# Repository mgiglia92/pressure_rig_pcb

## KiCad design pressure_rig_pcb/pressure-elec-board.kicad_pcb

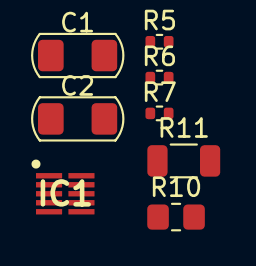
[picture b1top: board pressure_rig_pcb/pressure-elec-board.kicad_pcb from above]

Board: 2 copper layers, 8 parts (0 on the bottom side), 7 nets, no tracks yet.

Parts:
C1, C2: .1 uF; C_1206_3216Metric_Pad1.42x1.75mm
IC1: DAC82001DRXR; SON50P250X250X80-10N
R5, R6: 10 k; R_0402_1005Metric
R7: 5 k; R_0402_1005Metric
R10: 158k; R_0805_2012Metric_Pad1.20x1.40mm_HandSolder
R11: 30.1k; R_1206_3216Metric

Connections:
3.3V: C2.2 (-), IC1.10 (VREF)
5V: C1.2 (-), IC1.1 (VDD), R7.1 (+)
DAC_ACTIVE: IC1.7 (~SYNC), R7.2 (-)
GND: IC1.4 (AGND), R5.1 (+), R6.1 (+), R11.2
unnamed: IC1.3 (RSTSEL), R5.2 (-)
unnamed: IC1.5 (~RESET), R6.2 (-)
unnamed: R10.1, R11.1

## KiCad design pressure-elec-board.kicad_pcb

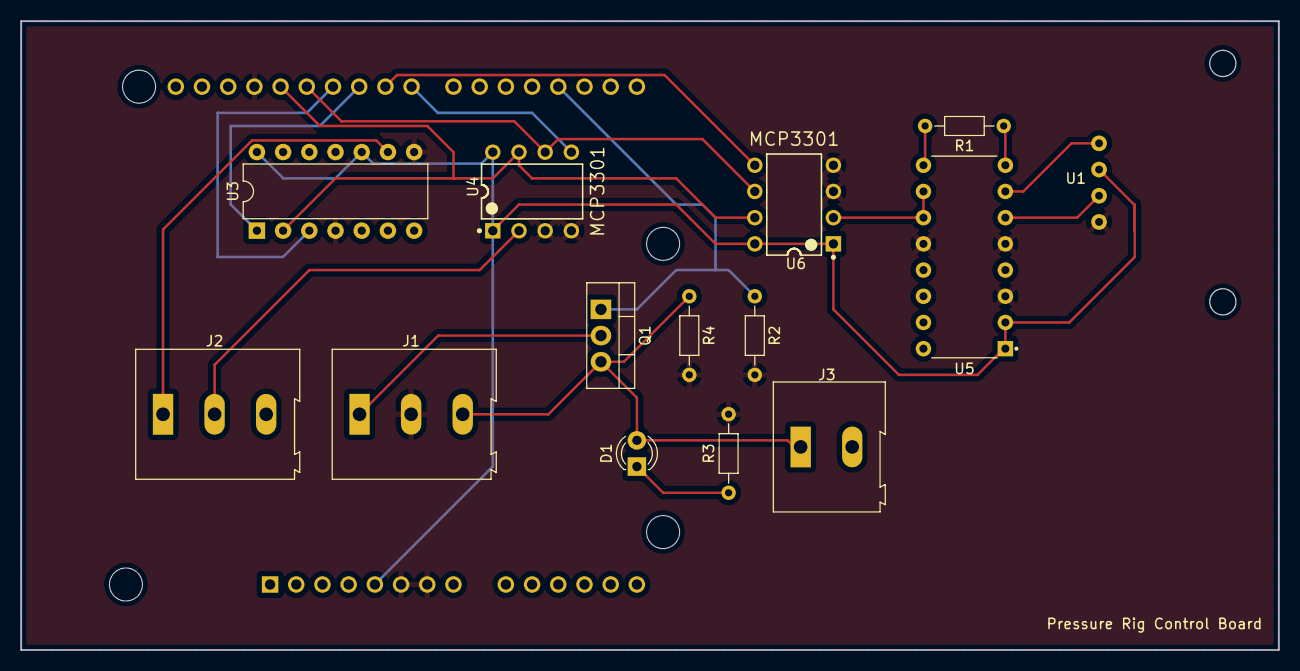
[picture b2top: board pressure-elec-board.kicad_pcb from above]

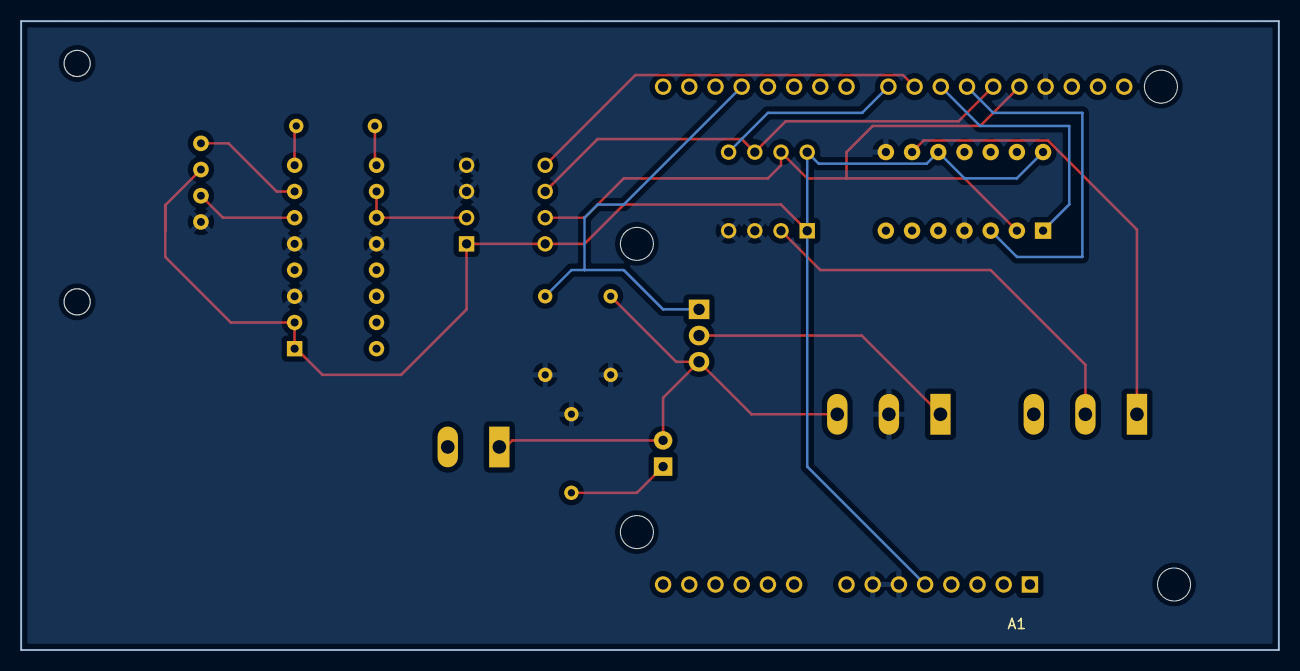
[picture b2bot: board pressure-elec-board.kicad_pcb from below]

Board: 2 copper layers, 121.9 x 60.9 mm, 15 parts (2 on the bottom side), 19 nets.

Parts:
A1: Arduino_UNO_R3; Arduino_SHIELD_UNO_R3_WithMountingHoles
D1: LED; LED_D3.0mm
J1, J2: Screw_Terminal_01x03; TerminalBlock_Altech_AK300-3_P5.00mm
J3: Screw_Terminal_01x03; TerminalBlock_Altech_AK300-2_P5.00mm
Q1: IRF540N; TO-220-3_Vertical
R1: 810; R_Axial_DIN0204_L3.6mm_D1.6mm_P7.62mm_Horizontal
R2, R4: 10k; R_Axial_DIN0204_L3.6mm_D1.6mm_P7.62mm_Horizontal
R3: 220; R_Axial_DIN0204_L3.6mm_D1.6mm_P7.62mm_Horizontal
U1: mpx2200; MPX2200
U3: MCP4251-xxxx-P; DIP-14_W7.62mm
U4, U6: MCP3301; Microchip-MCP3301-CI_P-Manufacturer_Recommended
U5: INA125P; ina125p_bigger_pads

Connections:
5V: A1.5 (+5V), U1.3 (V_supply), U3.10 (P0B), U3.14 (VDD), U4.1 (Vref), U4.8 (Vdd), U5.1 (V+), U5.2 (~SLEEP), U6.1 (Vref), U6.8 (Vdd)
12V: J1.1, Q1.2 (D)
ADC_1_ACTIVE: A1.24 (D9), U6.5 (~CS/SHDN)
ADC_2_ACTIVE: A1.23 (D8), U4.5 (~CS/SHDN)
CLK: A1.28 (D13), U3.2 (SCK), U4.7 (CLK), U6.7 (CLK)
D3: A1.18 (D3), Q1.1 (G), R2.1
DIGI_POT_ACTIVE: A1.25 (D10), U3.1 (~CS)
GND: A1.6 (GND), A1.7 (GND), A1.29 (GND), J1.2, R2.2, R3.2, R4.2, U1.1 (GND), U3.4 (VSS), U3.8 (P0A), U4.3 (IN-), U4.4 (Vss), U5.3 (V-), U5.5 (IAREF), U5.12 (VREFCOM), U6.3 (IN-), U6.4 (Vss)
MISO: A1.27 (D12), U4.6 (Dout), U6.6 (Dout)
MOSI: A1.26 (D11), U3.3 (SDI)
unnamed: D1.1 (K), R3.1
unnamed: R1.1, U5.8 (RG)
unnamed: R1.2, U5.9 (RG)
unnamed: U1.2 (+out), U5.6 (V+IN)
unnamed: U1.4 (-out), U5.7 (V-IN)
unnamed: U5.10 (VO), U5.11 (SENSE), U6.2 (IN+)
pressure_input: J2.1, U3.9 (P0W)
pressure_output: J2.2, U4.2 (IN+)
relay_module_input: D1.2 (A), J1.3, J3.1, Q1.3 (S), R4.1

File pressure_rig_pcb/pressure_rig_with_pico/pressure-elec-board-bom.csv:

"Id";"Designator";"Package";"Quantity";"Designation";"Supplier and ref";
1;"J3";"TerminalBlock_Altech_AK300-2_P5.00mm";1;"Screw_Terminal_01x03";;;
2;"U1";"MPX2200";1;"mpx2200";;;
3;"R3";"R_Axial_DIN0204_L3.6mm_D1.6mm_P7.62mm_Horizontal";1;"220";;;
4;"U5";"ina125p_bigger_pads";1;"INA125P";;;
5;"J1,J2";"TerminalBlock_Altech_AK300-3_P5.00mm";2;"Screw_Terminal_01x03";;;
6;"D1";"LED_D3.0mm";1;"LED";;;
7;"R1";"R_Axial_DIN0204_L3.6mm_D1.6mm_P7.62mm_Horizontal";1;"810";;;
8;"R2,R4";"R_Axial_DIN0204_L3.6mm_D1.6mm_P7.62mm_Horizontal";2;"10k";;;
9;"U3";"DIP-14_W7.62mm";1;"MCP4251-xxxx-P";;;
10;"Q1";"TO-220-3_Vertical";1;"IRF540N";;;
11;"U4,U6";"Microchip-MCP3301-CI_P-Manufacturer_Recommended";2;"MCP3301";;;
12;"A1";"Arduino_SHIELD_UNO_R3_WithMountingHoles";1;"Arduino_UNO_R3";;;

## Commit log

2023-04-01 pressure rig pcb but with pico not arduino
2023-04-01 Pressure rig implementation with pico controller
2023-04-14 pressure rig using pico
